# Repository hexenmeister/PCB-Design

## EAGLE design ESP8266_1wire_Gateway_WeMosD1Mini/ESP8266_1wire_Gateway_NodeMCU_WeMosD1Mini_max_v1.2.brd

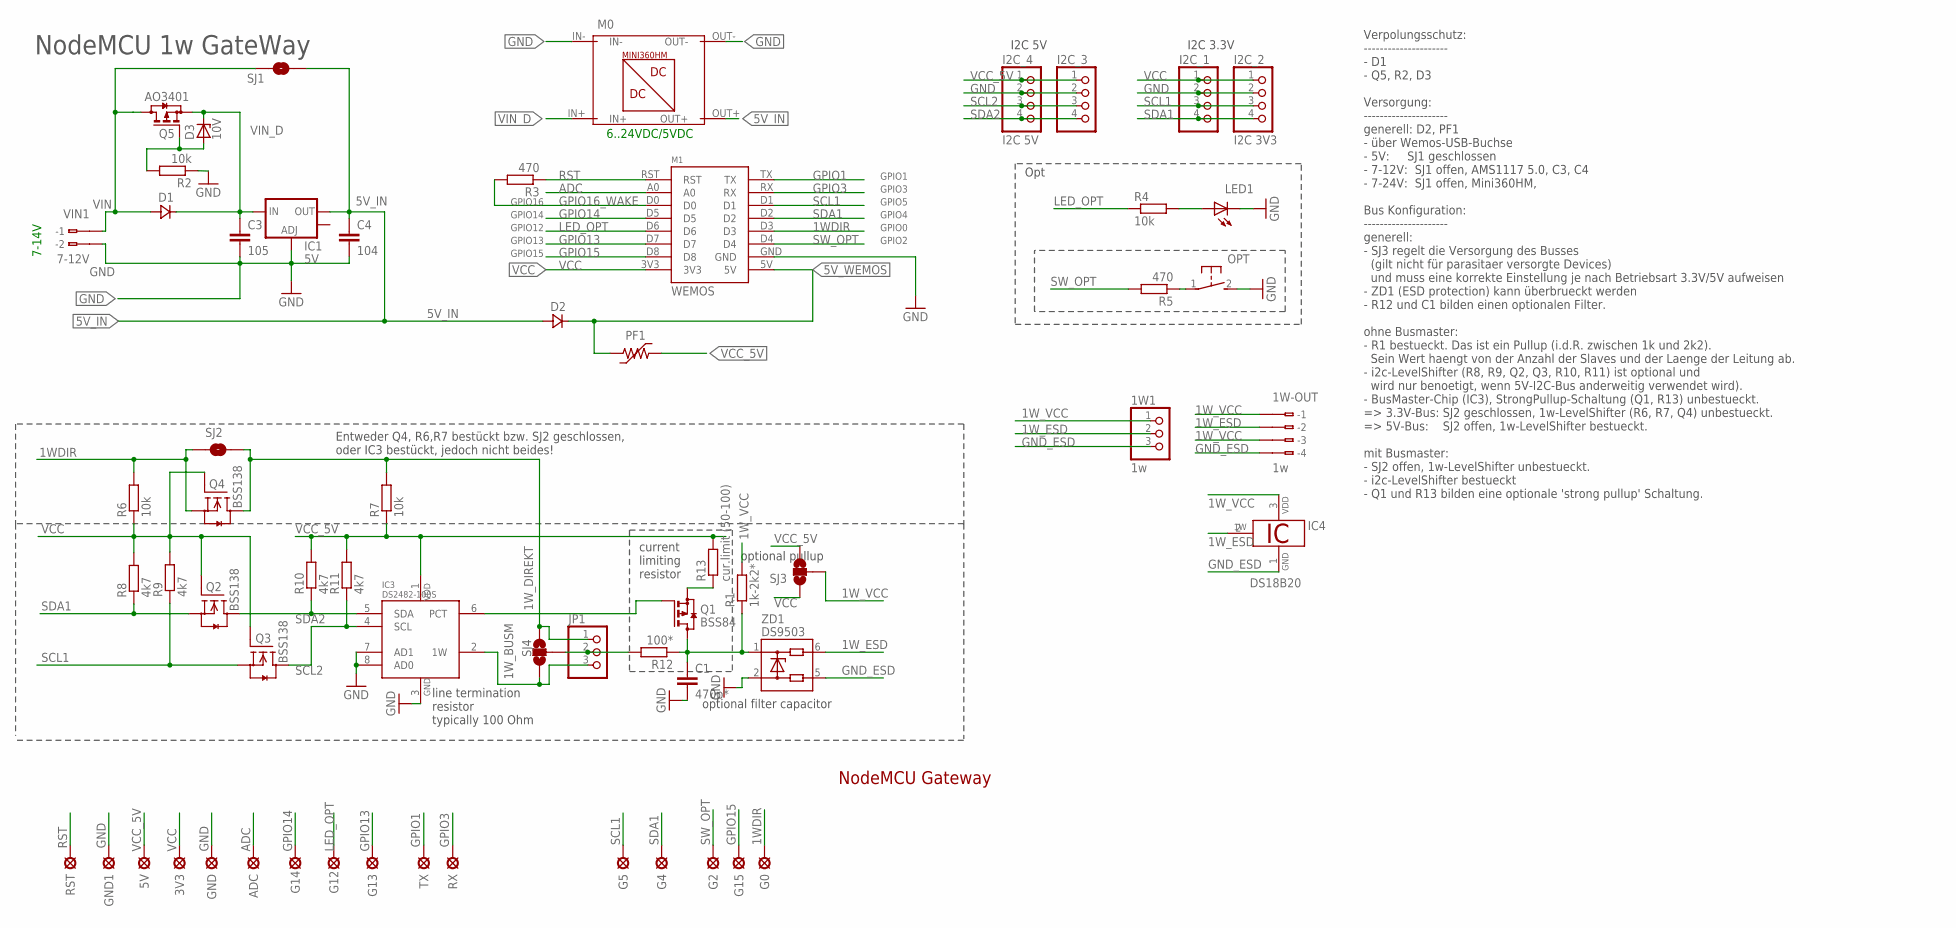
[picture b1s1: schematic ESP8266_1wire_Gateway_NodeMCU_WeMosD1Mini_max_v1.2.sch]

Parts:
1W1: 1w; 1X03
1W-OUT: 1w; CON_350-104
3V3, 5V: LSP10
ADC: LSP10
C1: 470p*; C0805
C3: 105; C0805
C4: 104; C0805
D1, D2: SS14; DO214
D3: 10V; SOD80C_LONG_PADS
G0, G2, G4, G5, G12, G13, G14, G15: LSP10
GND: LSP10
GND1: GND; LSP10
I2C_1, I2C_3: 1X04
I2C_2: I2C 3V3; 1X04
I2C_4: I2C 5V; 1X04
IC1: 5V; SOT223
IC3: DS2482-100S; SO08
IC4: DS18B20; TO92-
JP1: PINHD-1X3_S; 1X03
LED1: CFG; CHIPLED_1206
M0: MINI360HMTHROUGH-HOLE; MINI360HM
M1: WEMOS
OPT: OPT; DTSM-3
PF1: 500mA; F1206
Q1: BSS84; SOT23
Q2, Q3, Q4: BSS138; SOT23
Q5: AO3401; SOT23
R1: 1k-2k2*; R0805
R2: 10k; R0805_SMALL_GAP
R3, R5: 470; R0805
R4, R6, R7: 10k; R0805
R8, R9, R10, R11: 4k7; R0805
R12: 100*; R0805_SMALL_GAP
R13: cur.limit (50-100); R0805_SMALL_GAP
RST: RST; LSP10
RX: LSP10
SJ1: bypass vr; PAD-JUMPER-2-NO_YES_SILK
SJ2: bypass; PAD-JUMPER-2-NO_YES_SILK
SJ3: 5V | 3V3; PAD-JUMPER-3-NO_YES_SILK
SJ4: direct | busmaster; PAD-JUMPER-3-NO_YES_SILK
TX: LSP10
VIN1: 7-12V; CON_350-102
ZD1: DS9503; TSOC6_BYPASS_J

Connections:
1WDIR: G0.1, M1.D3, Q4.2 (S), R6.2, SJ2.1
1W_: C1.1, Q1.3 (D), R1.1, R12.1, ZD1.1
1W_BUSM: IC3.2 (1W), JP1.3, SJ4.1
1W_DIREKT: JP1.1, Q4.3 (D), R7.2, SJ2.2, SJ4.3
1W_ESD: 1W1.2, 1W-OUT.B2 (B-2), IC4.2 (1W), ZD1.6
1W_OUT: JP1.2, R12.2, SJ4.2
1W_VCC: 1W1.1, 1W-OUT.B1 (B-1), 1W-OUT.B3 (B-3), IC4.3 (VDD), R1.2, SJ3.2
5V_IN: C4.1, D2.ANODE, IC1.2 (OUT), M0.OUT+, SJ1.2
5V_WEMOS: D2.CATHODE, M1.5V, PF1.2
ADC: ADC.1, M1.A0
GND: C1.2, C3.2, C4.2, GND.1, GND1.1, I2C_1.2, I2C_2.2, I2C_3.2, I2C_4.2, IC1.1 (ADJ), IC3.3 (GND), IC3.7 (AD1), IC3.8 (AD0), LED1.C, M0.IN-, M0.OUT-, M1.GND, OPT.2, R2.1, VIN1.B2 (B-2), ZD1.2
GND_ESD: 1W1.3, 1W-OUT.B4 (B-4), IC4.1 (GND), ZD1.5
GPIO1: M1.TX, TX.1
GPIO3: M1.RX, RX.1
GPIO13: G13.1, M1.D7
GPIO14: G14.1, M1.D5
GPIO15: G15.1, M1.D8
GPIO16_WAKE: M1.D0, R3.2
LED_OPT: G12.1, M1.D6, R4.1
unnamed: LED1.A, R4.2
unnamed: D3.A, Q5.1 (G), R2.2
unnamed: IC3.6 (PCT), Q1.1 (G)
unnamed: Q1.2 (S), R13.1
unnamed: OPT.1, R5.1
RST: M1.RST, R3.1, RST.1
SCL1: G5.1, I2C_1.3, I2C_2.3, M1.D1, Q3.2 (S), R9.1
SCL2: I2C_3.3, I2C_4.3, IC3.4 (SCL), Q3.3 (D), R11.1
SDA1: G4.1, I2C_1.4, I2C_2.4, M1.D2, Q2.2 (S), R8.1
SDA2: I2C_3.4, I2C_4.4, IC3.5 (SDA), Q2.3 (D), R10.1
SW_OPT: G2.1, M1.D4, R5.2
VCC: 3V3.1, I2C_1.1, I2C_2.1, M1.3V3, Q2.1 (G), Q3.1 (G), Q4.1 (G), R6.1, R8.2, R9.2, SJ3.1
VCC_5V: 5V.1, I2C_3.1, I2C_4.1, IC3.1 (VDD), PF1.1, R7.1, R10.2, R11.2, R13.2, SJ3.3
VIN: D1.ANODE, Q5.3 (D), SJ1.1, VIN1.B1 (B-1)
VIN_D: C3.1, D1.CATHODE, D3.C, IC1.3 (IN), M0.IN+, Q5.2 (S)

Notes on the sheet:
NodeMCU Gateway
NodeMCU 1w GateWay
7-14V
line termination resistor typically 100 Ohm
current limiting resistor
Opt
GPIO16
GPIO5
GPIO4
GPIO0
GPIO2
GPIO14
GPIO12
GPIO13
GPIO15
GPIO3
GPIO1
optional filter capacitor
Entweder Q4, R6,R7 bestückt bzw. SJ2 geschlossen, oder IC3 bestückt, jedoch nicht beides!
optional pullup
I2C 5V
I2C 3.3V
Verpolungsschutz: --------------------- - D1 - Q5, R2, D3 Versorgung: --------------------- generell: D2, PF1 - über Wemos-USB-Buchse - 5V: SJ1 geschlossen - 7-12V: SJ1 offen, AMS1117 5.0, C3, C4 - 7-24V: SJ1 offen, Mini360HM, Bus Konfiguration: --------------------- generell: - SJ3 regelt die Vers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
6..24VDC/5VDC

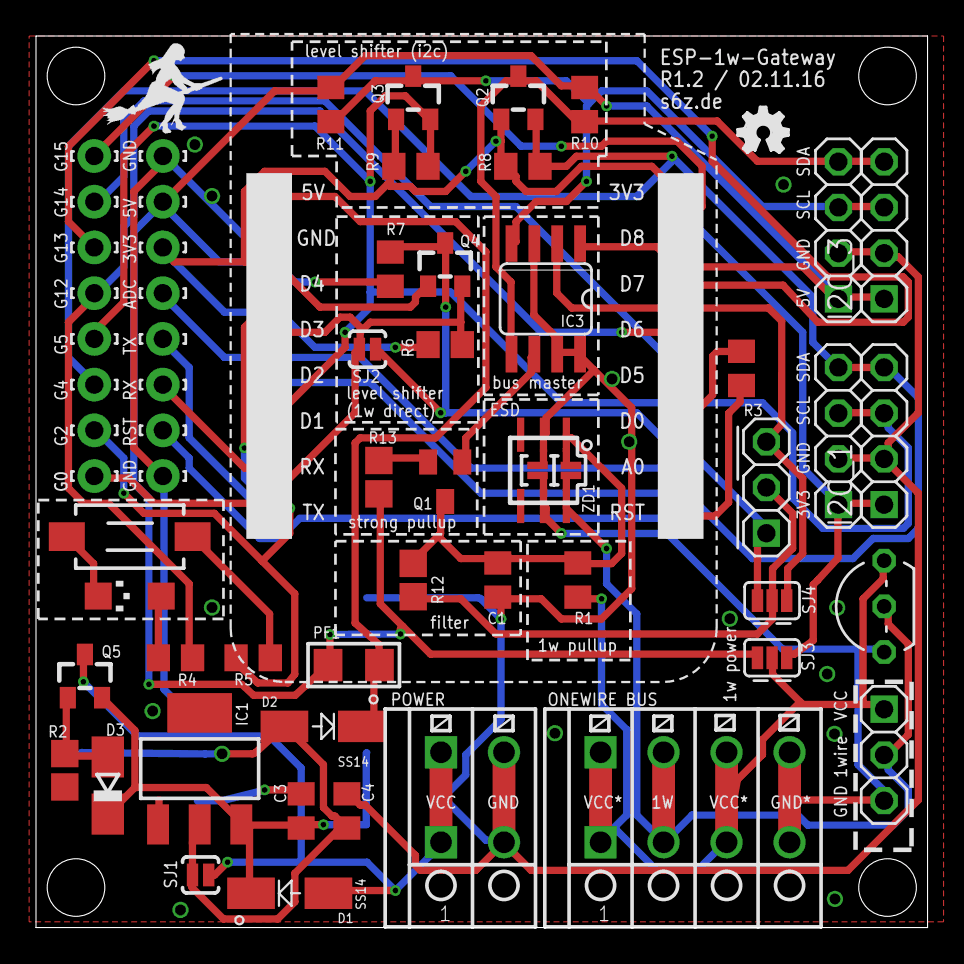
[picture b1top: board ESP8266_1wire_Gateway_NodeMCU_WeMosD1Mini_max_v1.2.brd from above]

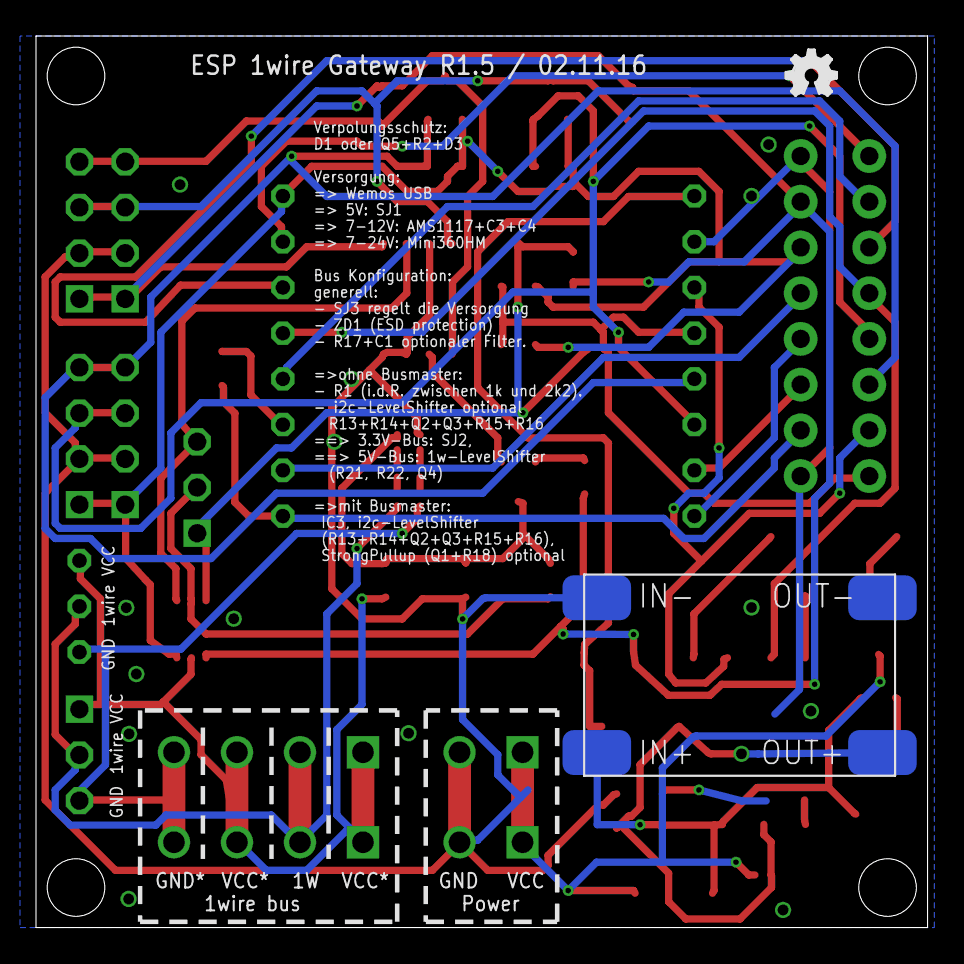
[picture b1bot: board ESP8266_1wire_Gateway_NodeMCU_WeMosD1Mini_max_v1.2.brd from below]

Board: 2 copper layers, 49.5 x 49.5 mm, 63 parts (2 on the bottom side), 34 nets.

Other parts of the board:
U$1, U$2: OSHW_FILLX100_NOTEXT

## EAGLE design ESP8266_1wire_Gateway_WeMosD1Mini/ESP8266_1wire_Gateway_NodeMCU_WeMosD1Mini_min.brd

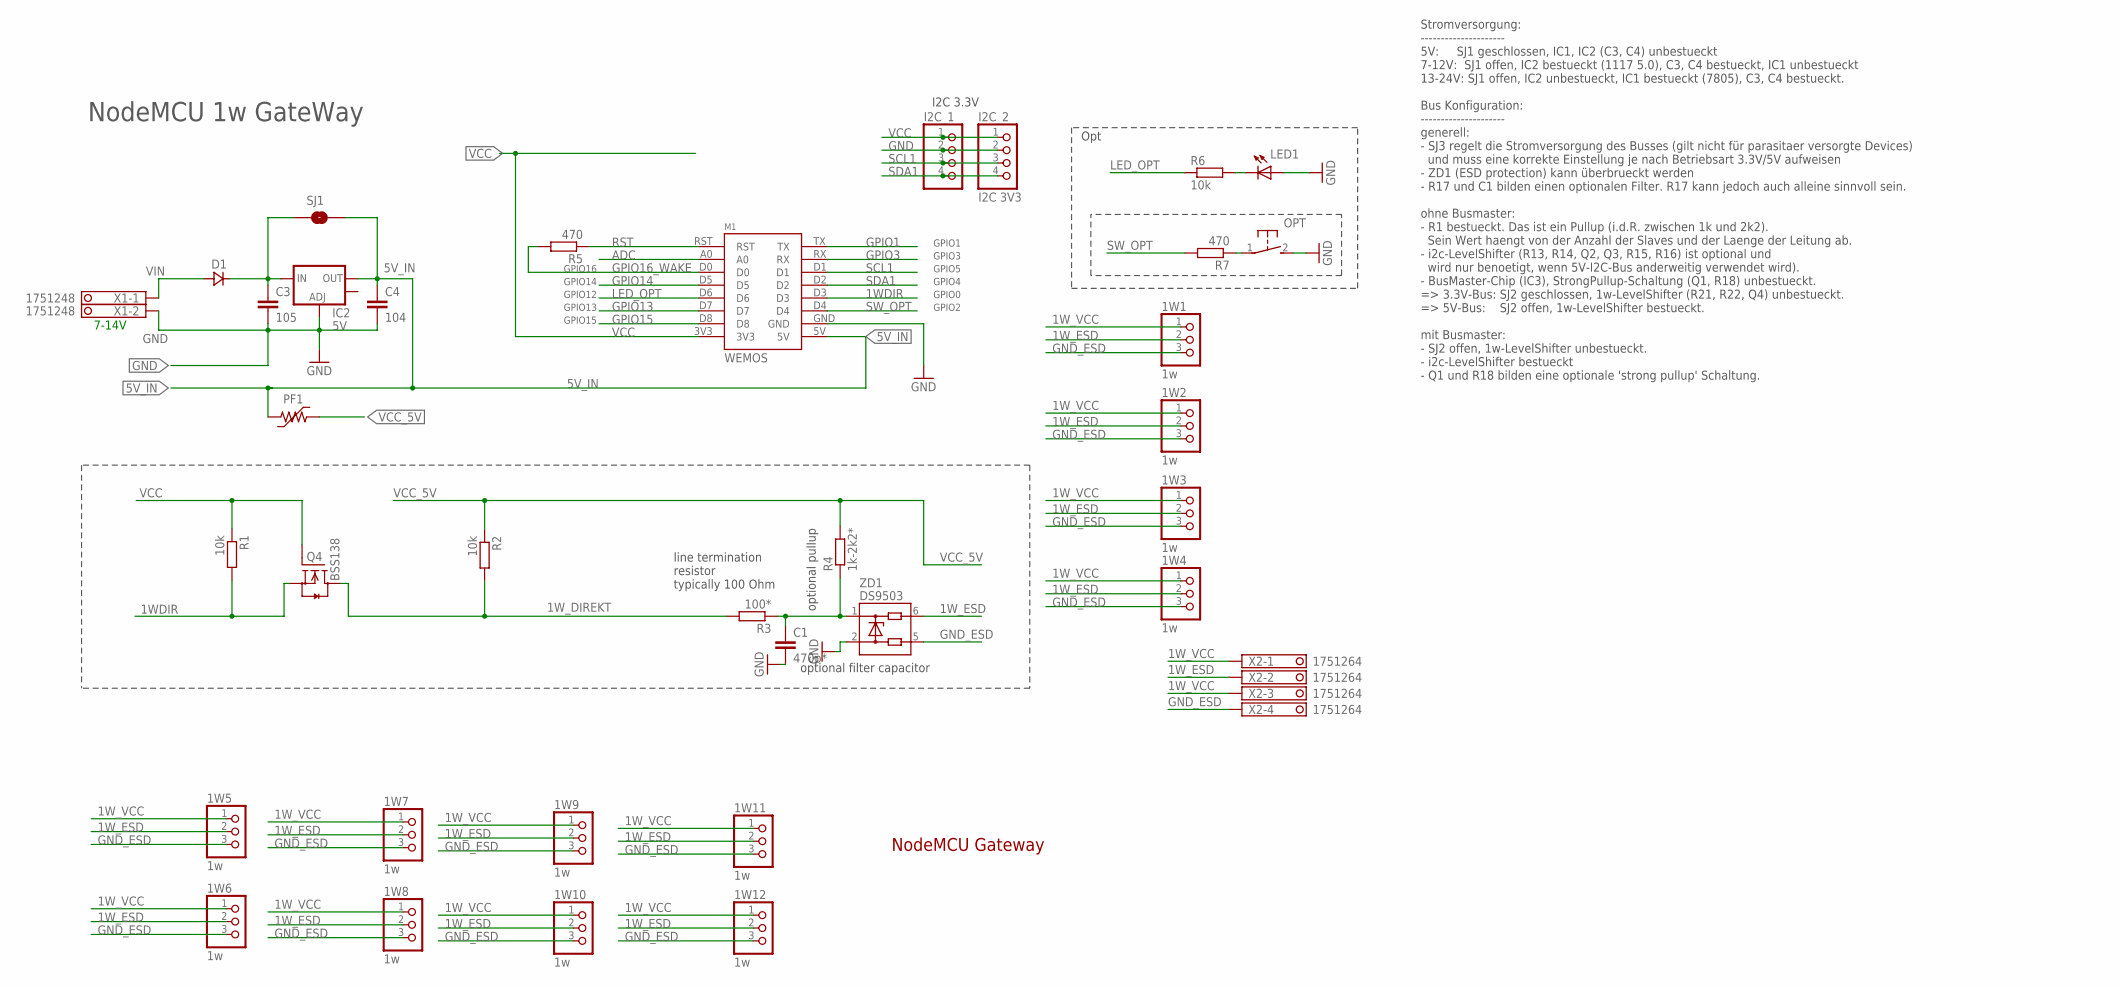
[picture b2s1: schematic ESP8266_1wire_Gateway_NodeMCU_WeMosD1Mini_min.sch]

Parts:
1W1, 1W2, 1W3, 1W4, 1W5, 1W6, 1W7, 1W8, 1W9, 1W10, 1W11, 1W12: 1w; 1X03
C1: 470p*; C0805
C3: 105; C0805
C4: 104; C0805
D1: SS14; DO214
I2C_1: 1X04
I2C_2: I2C 3V3; 1X04
IC2: 5V; SOT223
LED1: CFG; CHIPLED_1206
M1: WEMOS
OPT: OPT; DTSM-3
PF1: 500mA; F1206
Q4: BSS138; SOT23
R1, R2, R6: 10k; R0805
R3: 100*; R0805_SMALL_GAP
R4: 1k-2k2*; R0805
R5, R7: 470; R0805
SJ1: bypass vreg; PAD-JUMPER-2-NO_YES_SILK
X1: 1751248
X2: 1751264
ZD1: DS9503; TSOC6_BYPASS_J

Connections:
1WDIR: M1.D3, Q4.2 (S), R1.2
1W_: C1.1, R3.1, R4.1, ZD1.1
1W_DIREKT: Q4.3 (D), R2.2, R3.2
1W_ESD: 1W1.2, 1W2.2, 1W3.2, 1W4.2, 1W5.2, 1W6.2, 1W7.2, 1W8.2, 1W9.2, 1W10.2, 1W11.2, 1W12.2, X2.2, ZD1.6
1W_VCC: 1W1.1, 1W2.1, 1W3.1, 1W4.1, 1W5.1, 1W6.1, 1W7.1, 1W8.1, 1W9.1, 1W10.1, 1W11.1, 1W12.1, X2.1, X2.3
5V_IN: C4.1, IC2.2 (OUT), M1.5V, PF1.2, SJ1.2
ADC: M1.A0
GND: C1.2, C3.2, C4.2, I2C_1.2, I2C_2.2, IC2.1 (ADJ), LED1.A, M1.GND, OPT.2, X1.2, ZD1.2
GND_ESD: 1W1.3, 1W2.3, 1W3.3, 1W4.3, 1W5.3, 1W6.3, 1W7.3, 1W8.3, 1W9.3, 1W10.3, 1W11.3, 1W12.3, X2.4, ZD1.5
GPIO1: M1.TX
GPIO3: M1.RX
GPIO13: M1.D7
GPIO14: M1.D5
GPIO15: M1.D8
GPIO16_WAKE: M1.D0, R5.2
LED_OPT: M1.D6, R6.1
unnamed: LED1.C, R6.2
unnamed: C3.1, D1.CATHODE, IC2.3 (IN), SJ1.1
unnamed: OPT.1, R7.1
RST: M1.RST, R5.1
SCL1: I2C_1.3, I2C_2.3, M1.D1
SDA1: I2C_1.4, I2C_2.4, M1.D2
SW_OPT: M1.D4, R7.2
VCC: I2C_1.1, I2C_2.1, M1.3V3, Q4.1 (G), R1.1
VCC_5V: PF1.1, R2.1, R4.2
VIN: D1.ANODE, X1.1

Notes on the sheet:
NodeMCU Gateway
NodeMCU 1w GateWay
7-14V
line termination resistor typically 100 Ohm
Opt
GPIO16
GPIO5
GPIO4
GPIO0
GPIO2
GPIO14
GPIO12
GPIO13
GPIO15
GPIO3
GPIO1
optional filter capacitor
optional pullup
Stromversorgung: --------------------- 5V: SJ1 geschlossen, IC1, IC2 (C3, C4) unbestueckt 7-12V: SJ1 offen, IC2 bestueckt (1117 5.0), C3, C4 bestueckt, IC1 unbestueckt 13-24V: SJ1 offen, IC2 unbestueckt, IC1 bestueckt (7805), C3, C4 bestueckt. Bus Konfiguration: --------------------- generell: - SJ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
I2C 3.3V

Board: 2 copper layers, 37 parts (1 on the bottom side), 20 nets, no tracks yet.

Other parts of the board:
U$1, U$2: OSHW_FILLX100_NOTEXT

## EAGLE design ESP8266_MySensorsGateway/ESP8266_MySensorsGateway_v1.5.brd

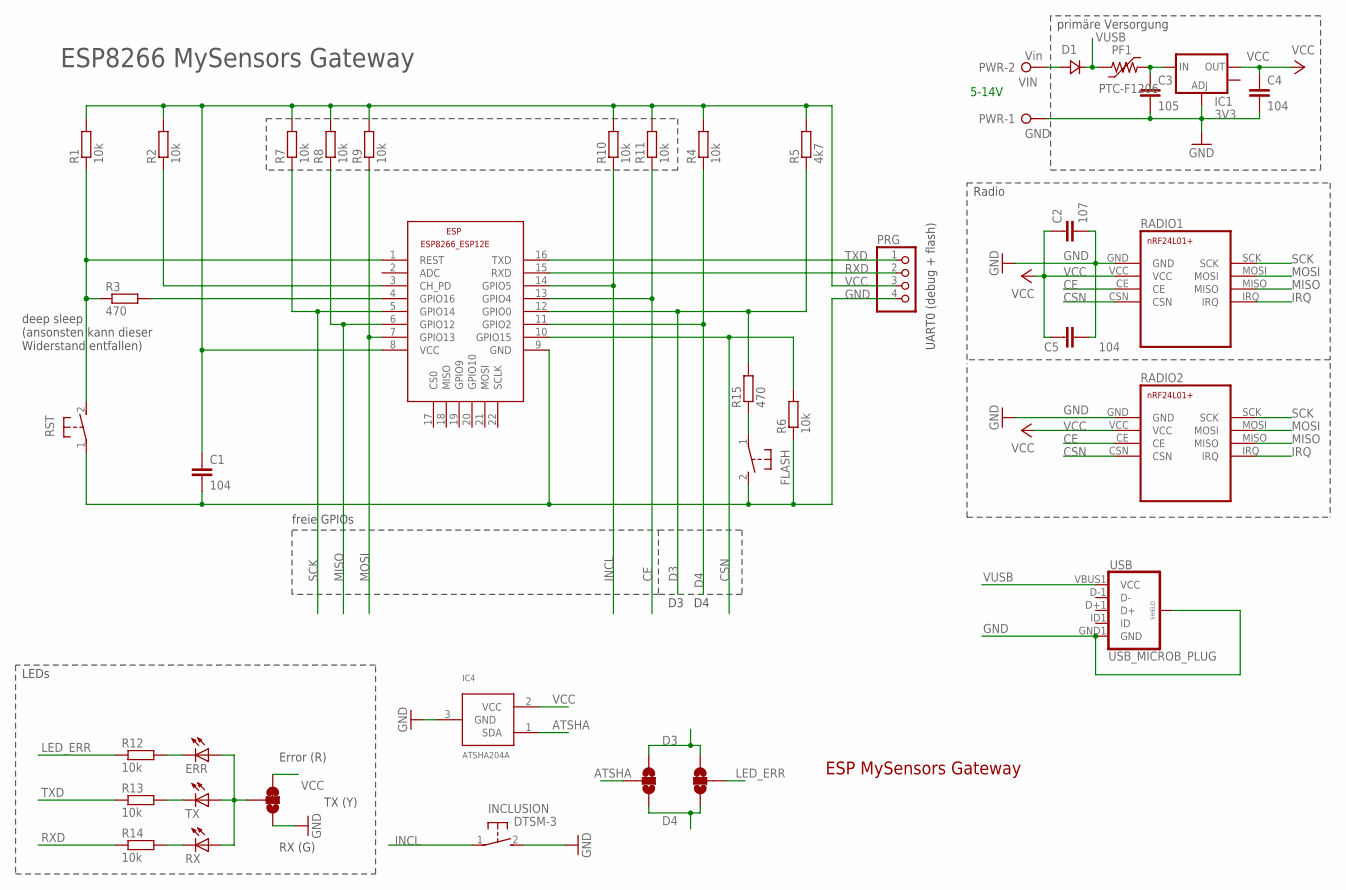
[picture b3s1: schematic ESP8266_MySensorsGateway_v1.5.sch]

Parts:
C1, C4, C5: 104; C0805
C2: 107; MY1210
C3: 105; C0805
D1: SS14; DO214
ERR: R; CHIPLED_1206
ESP: µC; ESP8266-ESP12E
FLASH: DTSM-3
IC1: 3V3; SOT223
IC4: ATSHA204A; SOT23
INCLUSION: DTSM-3
PF1: PTC-F1206; F1206
PRG: 1X04
PWR: Vin; W237-132
R1, R2, R4, R6, R7, R8, R9, R10, R11, R12, R13, R14: 10k; R0805
R3, R15: 470; R0805
R5: 4k7; R0805
RADIO1: NRF24L01+
RADIO2: NRF24L01+NRF24L01+MINI; NRF24L01+MINI
RST: DTSM-3
RX: G; CHIPLED_1206
SJ1: JUMPER-PAD-3-2OF3_NC_BY_TRACE_SMALL; PAD-JUMPER-3-2OF3_NC_BY_TRACE_YES_SILK_FULL_BOX
SJ2, SJ3: JUMPER-PAD-3-NOYES_SILK; PAD-JUMPER-3-NO_YES_SILK
TX: Y; CHIPLED_1206
USB: USB_MICROB_PLUG; USB-B-MICRO-SMD_V03_HOLE

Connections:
ATSHA: IC4.1 (SDA), SJ2.2
CE: ESP.13 (GPIO4), R11.1, RADIO1.CE, RADIO2.CE
CH_PD: ESP.3 (CH_PD), R2.1
CSN: ESP.10 (GPIO15), R6.2, RADIO1.CSN, RADIO2.CSN
D3: ESP.12 (GPIO0), R5.1, R15.2, SJ2.3, SJ3.1
D4: ESP.11 (GPIO2), R4.1, SJ2.1, SJ3.3
DEEP_SLEEP: ESP.4 (GPIO16), R3.2
GND: C1.2, C2.2, C3.2, C4.2, C5.2, ESP.9 (GND), FLASH.2, IC1.1 (ADJ), IC4.3 (GND), INCLUSION.2, PRG.4, PWR.1, R6.1, RADIO1.GND, RADIO2.GND, RST.1, SJ1.1, USB.GND1 (GND), USB.SHIELD1 (SHIELD), USB.SHIELD2 (SHIELD), USB.SHIELD3 (SHIELD), USB.SLOT1 (SHIELD), USB.SLOT2 (SHIELD), USB.TAB1 (SHIELD), USB.TAB2 (SHIELD)
INCL: ESP.14 (GPIO5), INCLUSION.1, R10.1
IRQ: RADIO1.IRQ, RADIO2.IRQ
LED_ERR: R12.1, SJ3.2
L_BASE: ERR.A, RX.A, SJ1.2, TX.A
MISO: ESP.6 (GPIO12), R8.1, RADIO1.MISO, RADIO2.MISO
MOSI: ESP.7 (GPIO13), R9.1, RADIO1.MOSI, RADIO2.MOSI
unnamed: ERR.C, R12.2
unnamed: R13.2, TX.C
unnamed: R14.2, RX.C
unnamed: FLASH.1, R15.1
unnamed: C3.1, IC1.3 (IN), PF1.2
RST: ESP.1 (REST), R1.1, R3.1, RST.2
RXD: ESP.15 (RXD), PRG.2, R14.1
SCK: ESP.5 (GPIO14), R7.1, RADIO1.SCK, RADIO2.SCK
TXD: ESP.16 (TXD), PRG.1, R13.1
VCC: C1.1, C2.1, C4.1, C5.1, ESP.8 (VCC), IC1.2 (OUT), IC4.2 (VCC), PRG.3, R1.2, R2.2, R4.2, R5.2, R7.2, R8.2, R9.2, R10.2, R11.2, RADIO1.VCC, RADIO2.VCC, SJ1.3
VIN: D1.ANODE, PWR.2
VUSB: D1.CATHODE, PF1.1, USB.VBUS1 (VCC)

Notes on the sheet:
ESP MySensors Gateway
UART0 (debug + flash)
freie GPIOs
ESP8266 MySensors Gateway
deep sleep (ansonsten kann dieser Widerstand entfallen)
primäre Versorgung
5-14V
Radio
LEDs
Error (R)
TX (Y)
RX (G)

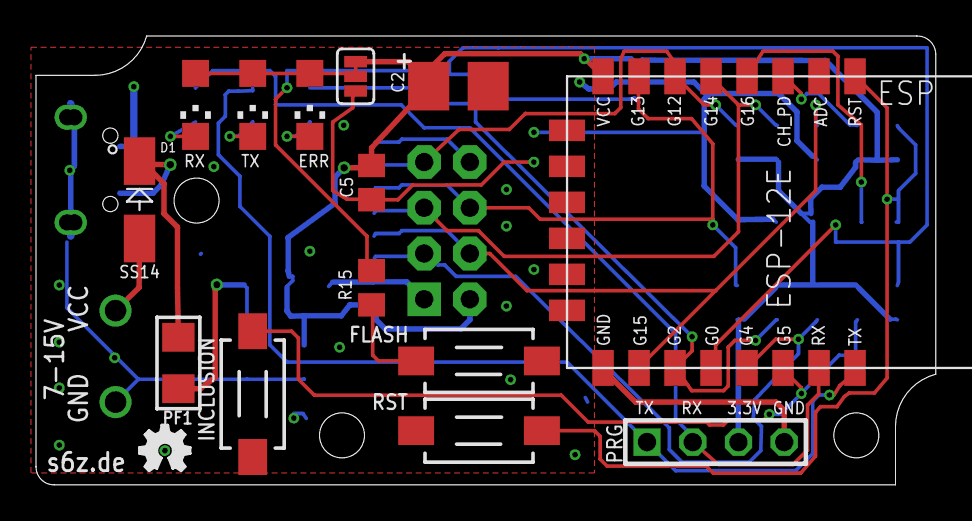
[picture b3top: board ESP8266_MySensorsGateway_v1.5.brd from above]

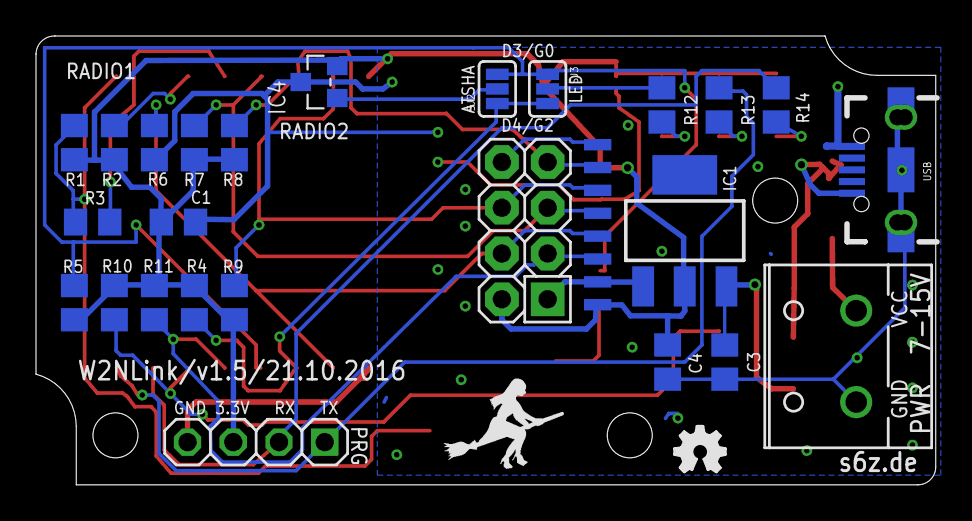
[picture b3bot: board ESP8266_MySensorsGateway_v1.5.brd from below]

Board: 2 copper layers, 50.0 x 24.9 mm, 41 parts (27 on the bottom side), 26 nets.

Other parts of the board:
U$1, U$2: OSHW_FILLX100_NOTEXT

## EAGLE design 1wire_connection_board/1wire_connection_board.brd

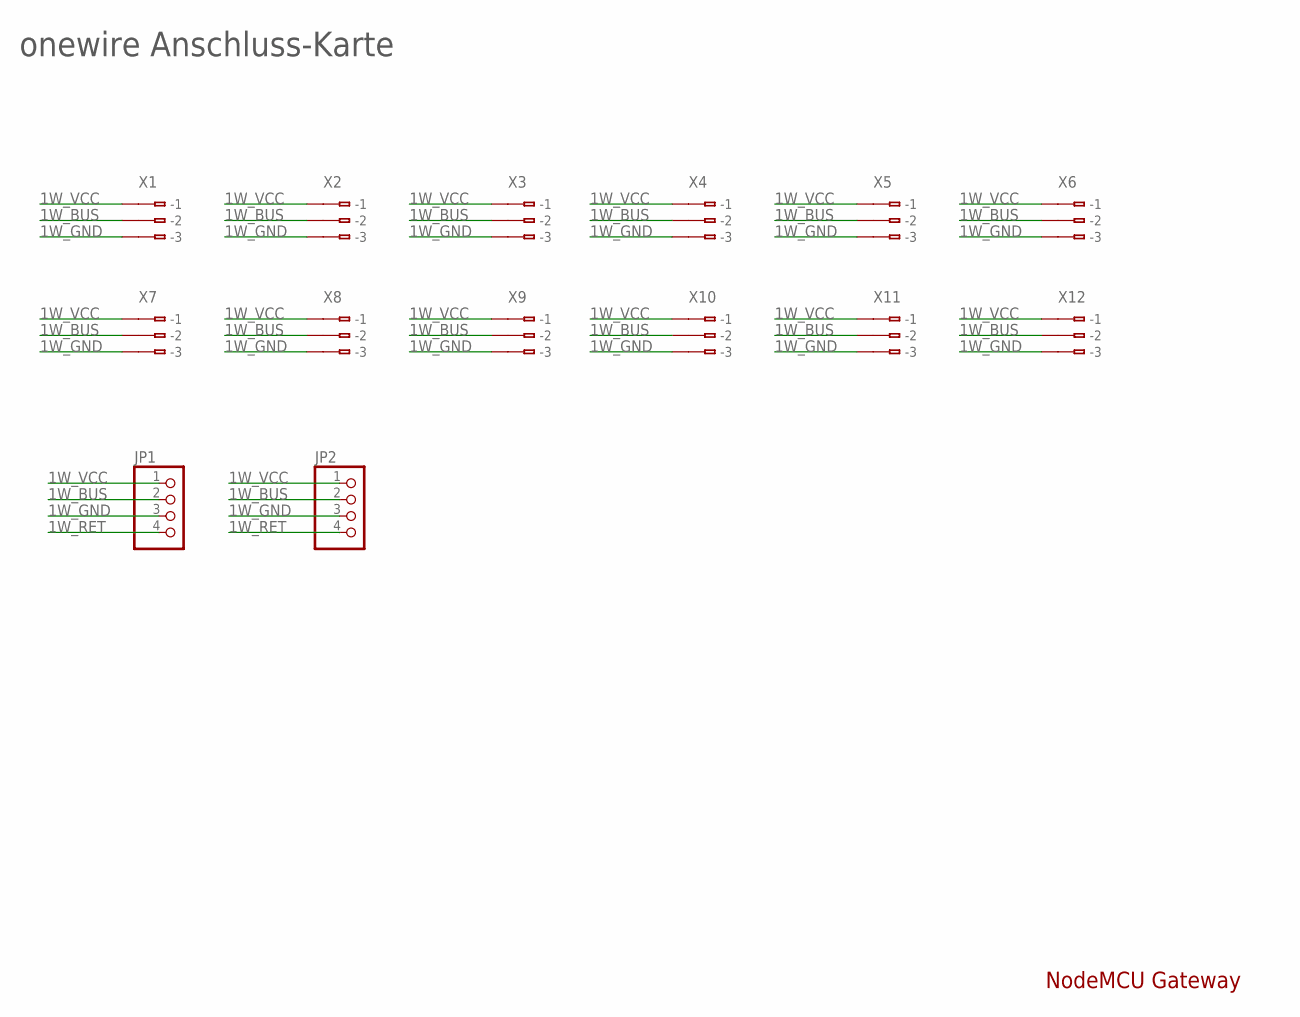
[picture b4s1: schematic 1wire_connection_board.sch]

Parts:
JP1, JP2: PINHD-1X4_S; 1X04
X1, X7: CON_350-103
X2, X3, X4, X5, X6, X8, X9, X10, X11, X12: CON_350-103OHNE_RAND; CON_350-103_O

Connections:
1W_BUS: JP1.2, JP2.2, X1.B2 (B-2), X2.B2 (B-2), X3.B2 (B-2), X4.B2 (B-2), X5.B2 (B-2), X6.B2 (B-2), X7.B2 (B-2), X8.B2 (B-2), X9.B2 (B-2), X10.B2 (B-2), X11.B2 (B-2), X12.B2 (B-2)
1W_GND: JP1.3, JP2.3, X1.B3 (B-3), X2.B3 (B-3), X3.B3 (B-3), X4.B3 (B-3), X5.B3 (B-3), X6.B3 (B-3), X7.B3 (B-3), X8.B3 (B-3), X9.B3 (B-3), X10.B3 (B-3), X11.B3 (B-3), X12.B3 (B-3)
1W_RET: JP1.4, JP2.4
1W_VCC: JP1.1, JP2.1, X1.B1 (B-1), X2.B1 (B-1), X3.B1 (B-1), X4.B1 (B-1), X5.B1 (B-1), X6.B1 (B-1), X7.B1 (B-1), X8.B1 (B-1), X9.B1 (B-1), X10.B1 (B-1), X11.B1 (B-1), X12.B1 (B-1)

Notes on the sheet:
NodeMCU Gateway
onewire Anschluss-Karte

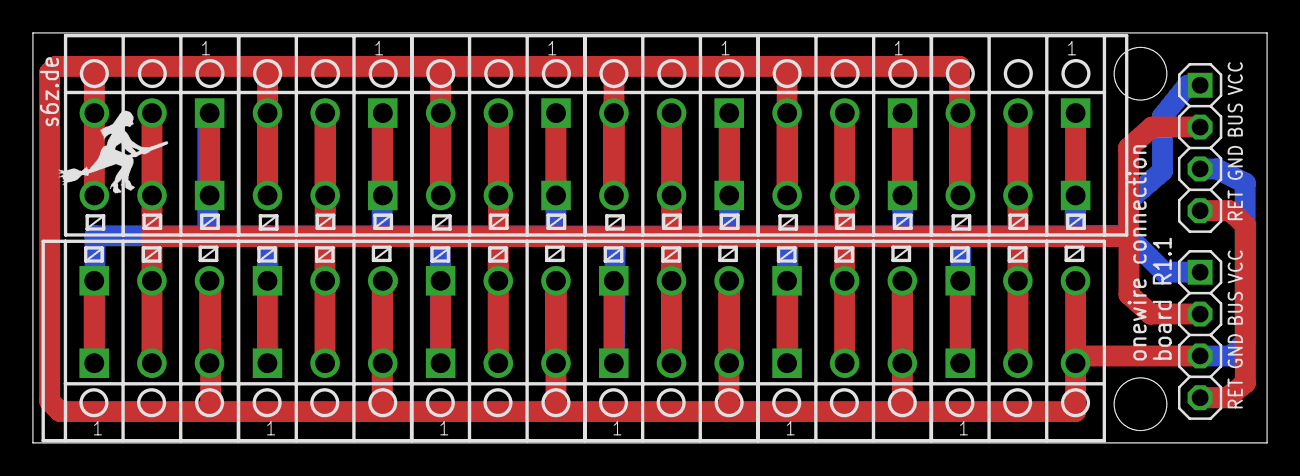
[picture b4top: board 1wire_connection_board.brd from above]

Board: 2 copper layers, 74.9 x 24.9 mm, 15 parts (1 on the bottom side), 4 nets.

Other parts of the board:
U$1: OSHW_FILLX100_NOTEXT

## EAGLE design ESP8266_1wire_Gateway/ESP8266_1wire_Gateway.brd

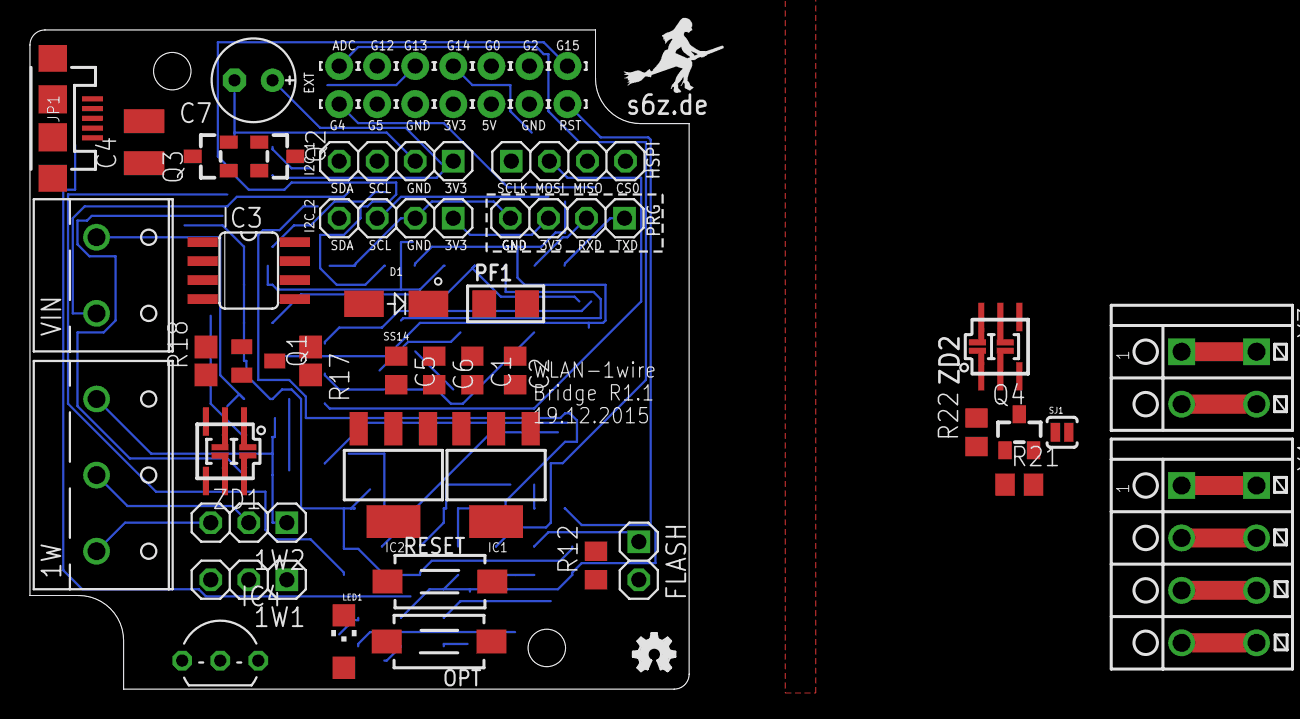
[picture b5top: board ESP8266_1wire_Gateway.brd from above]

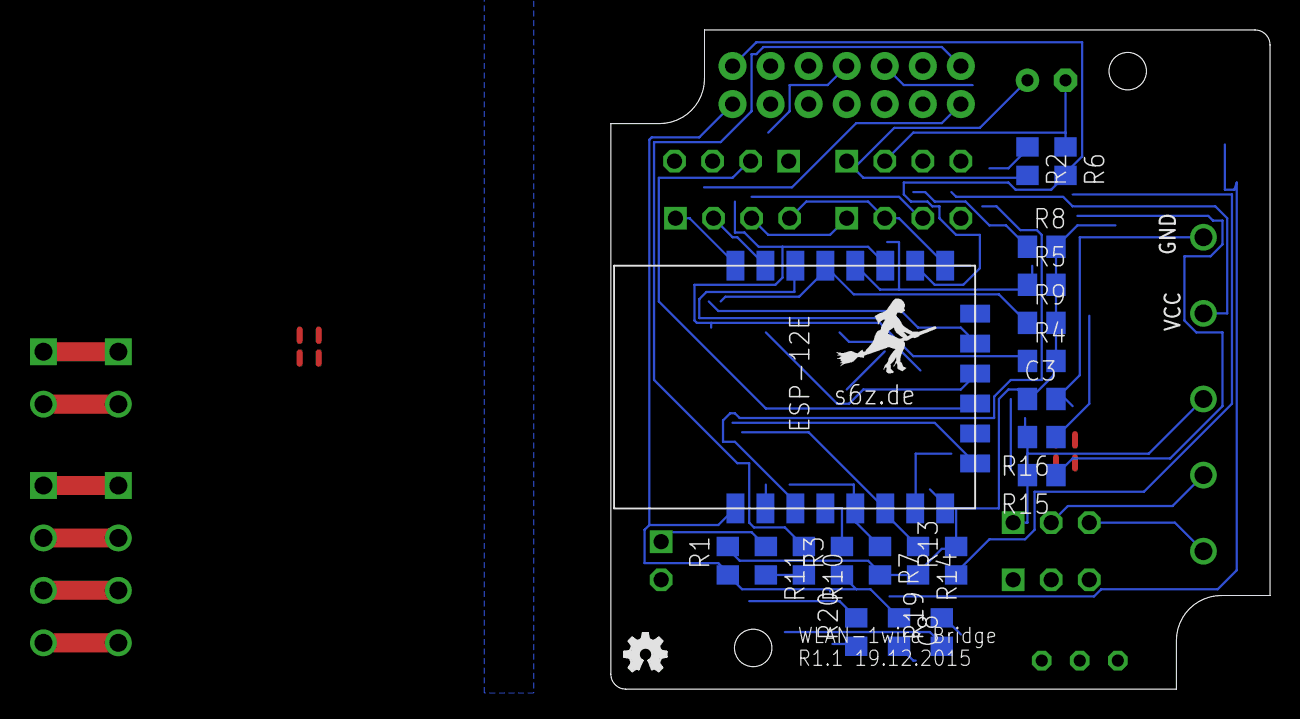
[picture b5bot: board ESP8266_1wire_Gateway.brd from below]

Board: 2 copper layers, 44.0 x 44.0 mm, 75 parts (21 on the bottom side), 37 nets.

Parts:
1W: 1Wire; W237-133
1W1, 1W2: 1X03
3V3, 5V: LSP10
ADC: LSP10
C1, C5: 105; C0805
C2, C6: 104; C0805
C3: 0,1mF; C0805
C4: 100mF; C1210
C7: 100uF; E2,5-6E
C8: 470pF; C0805
D1: SS14; DO214
FLASH: 1X02
G0, G2, G4, G5, G12, G13, G14, G15: LSP10
GND: LSP10
GND1: GND; LSP10
HSPI: 1X04
I2C_1, I2C_2: 1X04
IC1: 5V; SOT223
IC2: 3.3V; SOT223
IC3: DS2482-100S; SO08
IC4: DS18B20; TO92-
JP1: USB-MICROB
LED1: CFG; CHIPLED_1206
MDL1: µC; ESP8266-ESP12E
OPT: DTSM-3
PF1: 500mA; F1206
PRG: 1X04
Q1: BSS84; SOT23
Q2, Q3, Q4: BSS138; SOT23
R1, R2, R4, R5, R6, R7, R8, R9, R19, R21, R22: 10k; R0805
R3, R12, R20: 470; R0805
R10: 220k; R0805
R11: 100k; R0805
R13, R14, R15, R16: 4k7; R0805
R17: 100; R0805_SMALL_GAP
R18: ?; R0805_SMALL_GAP
RESET: DTSM-3
RST: RST; LSP10
SJ1: JUMPER-PAD-2-NOYES_SILK; PAD-JUMPER-2-NO_YES_SILK
U$1, U$2: OSHW_FILLX100_NOTEXT
VIN: 7-14; W237-132
X1: CON_350-104
X3: CON_350-102
ZD1, ZD2: DS9503_BYPASS_JP; TSOC6_BYPASS_J

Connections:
1W: IC3.2, R17.2
1WDIR: G0.1, MDL1.12, Q4.2, R5.1, R12.2, R21.2, SJ1.2
1W_: Q1.3, R17.1, ZD1.1
1W_1: Q4.3, R22.2, SJ1.1, ZD2.1
1W_ESD: 1W.2, 1W1.2, 1W2.2, IC4.2, ZD1.6
5V_IN: C2.1, IC1.2, JP1.VBUS, PF1.2
ADC: MDL1.2, R10.2, R11.2
CH_PD: MDL1.3, R2.1
DEEP_SLEEP: MDL1.4, R3.2
GND: C1.2, C2.2, C3.2, C4.2, C5.2, C6.2, C7.-, C8.2, FLASH.1, GND.1, GND1.1, I2C_1.2, I2C_2.2, IC1.1, IC2.1, IC3.3, IC3.7, IC3.8, JP1.GND, JP1.MT1, JP1.MT2, LED1.A, MDL1.9, OPT.2, PRG.4, R6.1, R11.1, RESET.1, VIN.1, ZD1.2, ZD2.2
GND_ESD: 1W.3, 1W1.3, 1W2.3, IC4.1, ZD1.5
GPIO13: G13.1, MDL1.7
GPIO14: G14.1, MDL1.5, R7.1
GPIO15: G15.1, MDL1.10, R6.2
HCS0: HSPI.4, MDL1.17
HMISO: HSPI.3, MDL1.18
HMOSI: HSPI.2, MDL1.21
HSCLK: HSPI.1, MDL1.22
LED_OPT: G12.1, MDL1.6, R19.1
unnamed: LED1.C, R19.2
unnamed: ADC.1, R10.1
unnamed: IC3.6, Q1.1
unnamed: Q1.2, R18.1
unnamed: C1.1, D1.CATHODE, IC1.3
unnamed: FLASH.2, R12.1
unnamed: OPT.1, R20.1
RST: C8.1, MDL1.1, R1.1, R3.1, RESET.2, RST.1
RXD: MDL1.15, PRG.2
SCL1: G5.1, I2C_1.3, I2C_2.3, MDL1.14, Q3.2, R8.1, R14.1
SCL2: IC3.4, Q3.3, R16.1
SDA1: G4.1, I2C_1.4, I2C_2.4, MDL1.13, Q2.2, R9.1, R13.1
SDA2: IC3.5, Q2.3, R15.1
SW_OPT: G2.1, MDL1.11, R4.1, R20.2
TXD: MDL1.16, PRG.1
VCC: 3V3.1, C3.1, C4.1, C6.1, C7.+, I2C_1.1, I2C_2.1, IC2.2, MDL1.8, PRG.3, Q2.1, Q3.1, Q4.1, R1.2, R2.2, R4.2, R5.2, R7.2, R8.2, R9.2, R13.2, R14.2, R21.1
VCC_5V: 1W.1, 1W1.1, 1W2.1, 5V.1, C5.1, IC2.3, IC3.1, IC4.3, PF1.1, R15.2, R16.2, R18.2, R22.1
VIN: D1.ANODE, VIN.2

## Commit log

2016-01-02 v1.2
2016-01-05 Version von 05.01.2016
2016-01-12 v0.9
2016-02-14 Version 1.2 : ELKO / THT Version 1.3 : tantal / SMD
2016-02-20 Richtige Datei eingecheckt
2016-02-20 .pro
2016-02-21 version 1.3
2016-02-28 kleinere optimierungen
2016-03-24 minor fixes (silk text)
2016-05-23 v.1.3
2016-05-23 fix (Radio GND), v.1.3.2
2016-05-26 fix: GND
2016-06-24 initial
2016-06-25 version 1.0
2016-06-25 update board
2016-06-30 rename
2016-07-31 v1.1: Beschriftungen
2016-09-01 i2c labels
2016-09-05 v1.3 (new diode to protect ams1117 by power over usb)
2016-10-23 USB-Buchse mit Bohrungen für einlötbaren Fähnchen
2016-10-25 Schutzdiode + Korrekturen
2016-11-03 MiniHM360

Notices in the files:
parts and their libraries:
SparkFun-PowerIC: Licensing: Creative Commons ShareAlike 4.0 International - https://creativecommons.org/licenses/by-sa/4.0
polyswitch: Copyright (C) 2008, Bob Starr
